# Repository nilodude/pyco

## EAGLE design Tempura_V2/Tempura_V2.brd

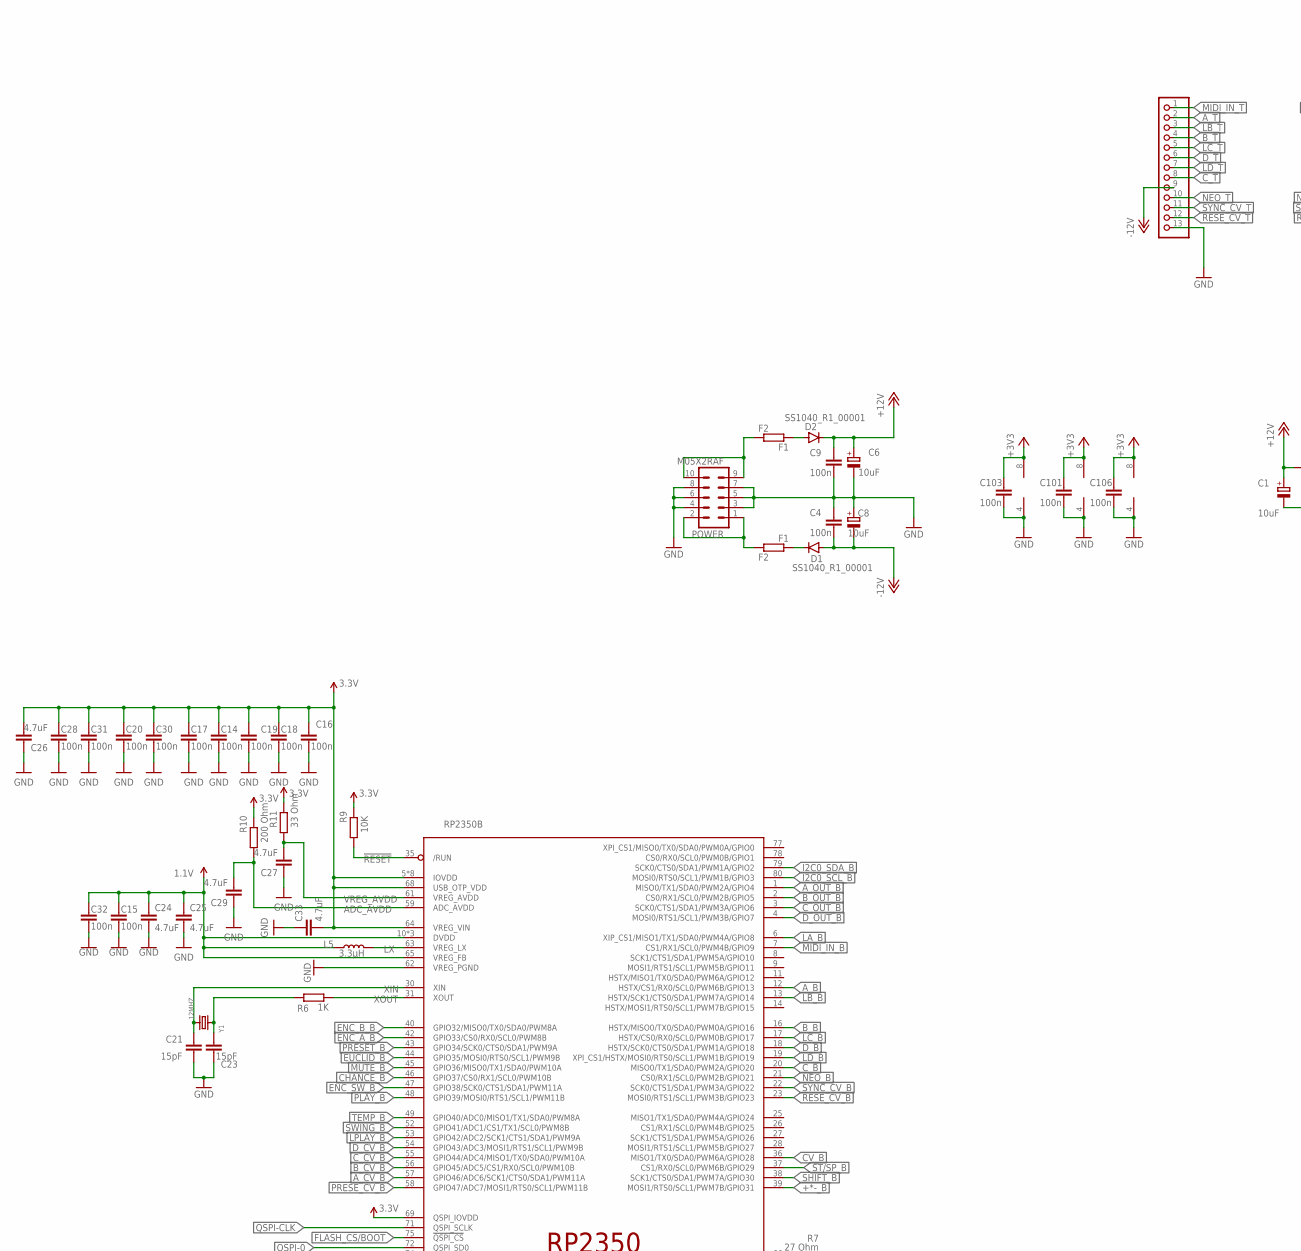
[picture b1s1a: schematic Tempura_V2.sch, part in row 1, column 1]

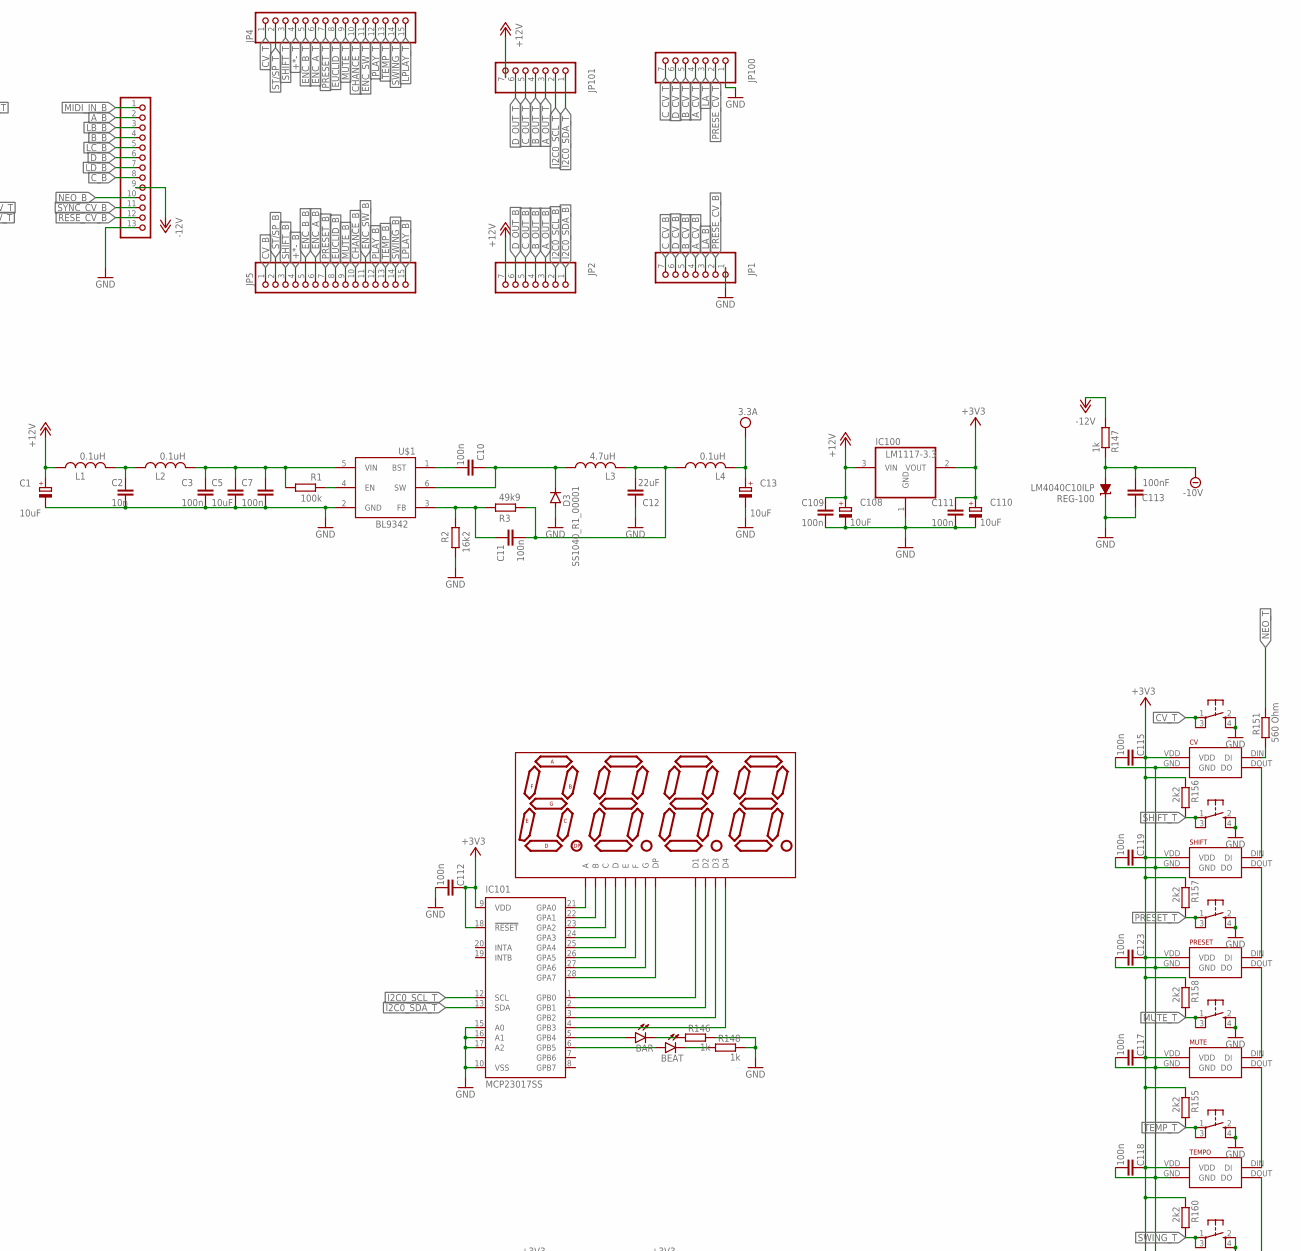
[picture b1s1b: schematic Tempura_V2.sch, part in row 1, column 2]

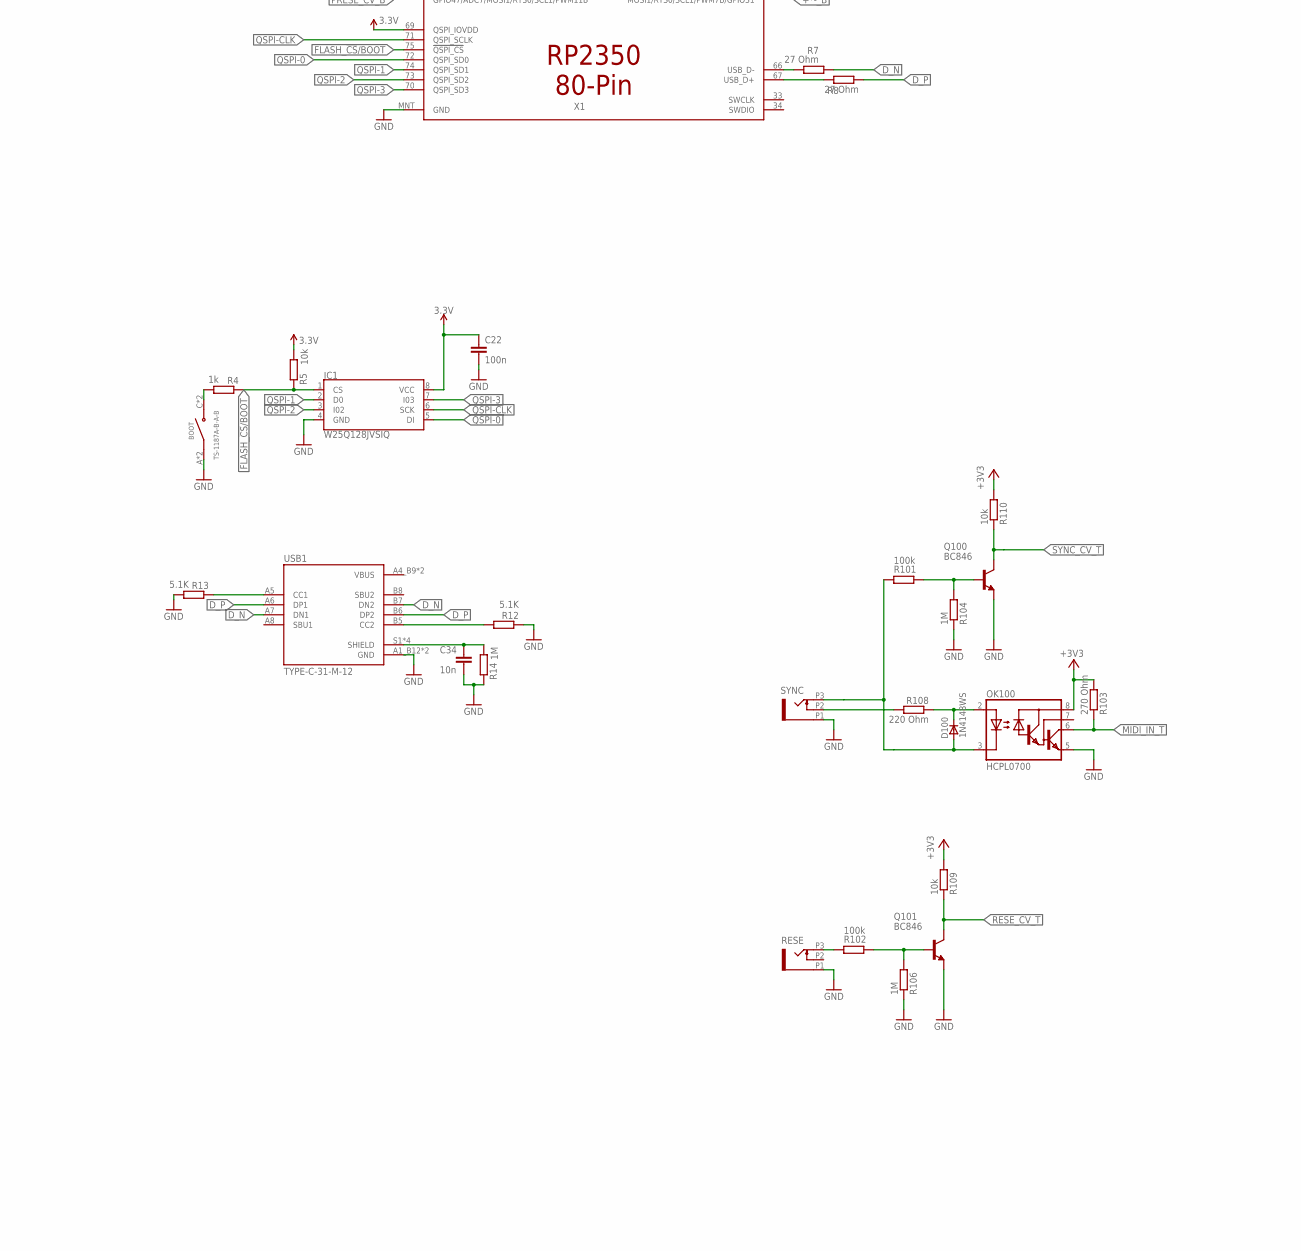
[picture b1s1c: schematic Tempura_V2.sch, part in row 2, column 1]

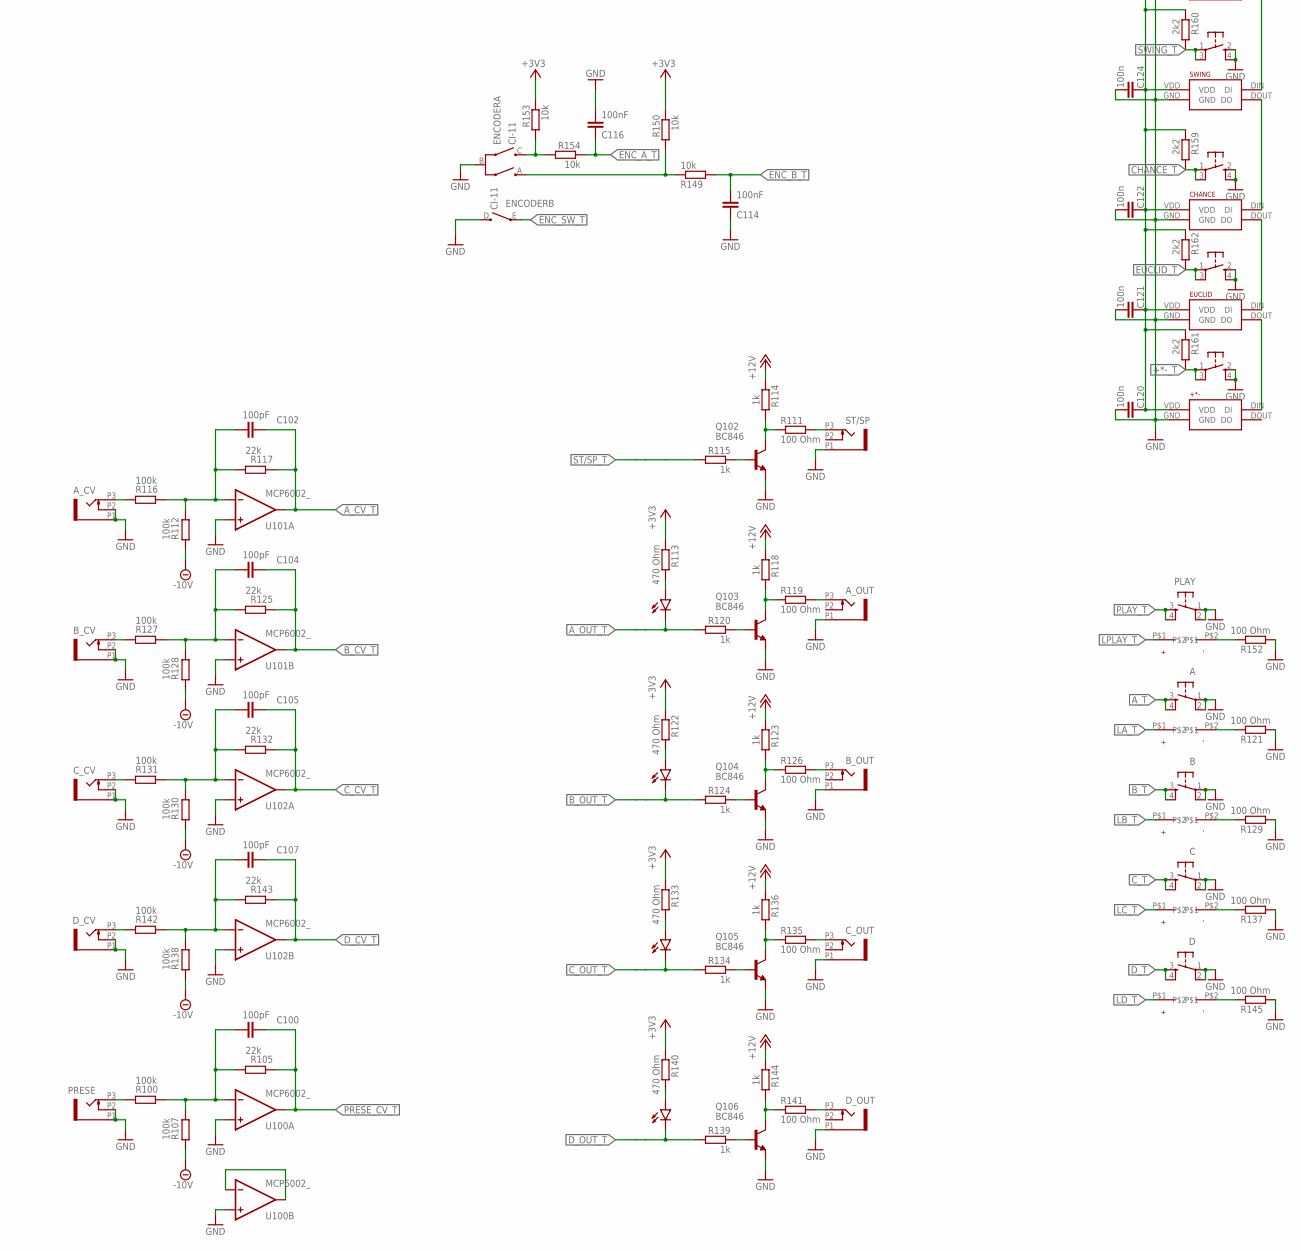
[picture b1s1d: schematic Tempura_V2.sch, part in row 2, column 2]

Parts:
+*-: BUTTON_NEOPIXELBUTTON_PIXEL_ç; BUTTON_PIXEL_ç
A: DTS-6_LED; TIMEBUTTON_HOLES_LEDS
A_CV: OG-PJ301_PJ301_THONKICONNNOHOLER; NOHOLER_GND_SHORT_PADMINI_GND
A_OUT: OG-PJ301_PJ301_THONKICONNNOHOLER; NOHOLER_GND_SHORT_PADMINI_GND
B: DTS-6_LED; TIMEBUTTON_HOLES_LEDS
BAR: OSG5TA7NE4B; LED3MM
BEAT: OSO5JA7NE4B; LED3MM
BOOT: TS-1187A-B-A-B; SW_TS-1187A-B-A-B
B_CV: OG-PJ301_PJ301_THONKICONNNOHOLER; NOHOLER_GND_SHORT_PADMINI_GND
B_OUT: OG-PJ301_PJ301_THONKICONNNOHOLER; NOHOLER_GND_SHORT_PADMINI_GND
C: DTS-6_LED; TIMEBUTTON_HOLES_LEDS
C1, C6, C8, C13, C108, C110: 10uF; PANASONIC_B
C2, C34: 10n; C0603
C3, C4, C7, C9, C10, C11, C22, C101, C103, C106, C109, C111, C112, C115, C117, C118, C119, C120, C121, C122, C123, C124: 100n; C0603
C5: 10uF; C0603
C12: 22uF; C0603
C14, C15, C16, C17, C18, C19, C20, C28, C30, C31, C32: 100n; 0603
C21, C23: 15pF; 0603
C24, C25: 4.7uF; 0603
C26: 4.7uF; C0603
C27, C29, C33: 4.7uF; C0805
C100, C102, C104, C105, C107: 100pF; C0603
C113, C114, C116: 100nF; C0603
CHANCE: BUTTON_NEOPIXELBUTTON_PIXEL_ç; BUTTON_PIXEL_ç
CV: BUTTON_NEOPIXELBUTTON_PIXEL_ç; BUTTON_PIXEL_ç
C_CV: OG-PJ301_PJ301_THONKICONNNOHOLER; NOHOLER_GND_SHORT_PADMINI_GND
C_OUT: OG-PJ301_PJ301_THONKICONNNOHOLER; NOHOLER_GND_SHORT_PADMINI_GND
D: DTS-6_LED; TIMEBUTTON_HOLES_LEDS
D1, D2, D3: SS1040_R1_00001; SOD123
D100: 1N4148WS; SOD323F
D_CV: OG-PJ301_PJ301_THONKICONNNOHOLER; NOHOLER_GND_SHORT_PADMINI_GND
D_OUT: OG-PJ301_PJ301_THONKICONNNOHOLER; NOHOLER_GND_SHORT_PADMINI_GND
ENCODER: CI-11
EUCLID: BUTTON_NEOPIXELBUTTON_PIXEL_ç; BUTTON_PIXEL_ç
F1: F2; R0603
F2: F1; R0603
IC1: W25Q128JVSIQ; SOIC-8
IC100: LM1117-3.3; SOT223
IC101: MCP23017SS; SSOP28
JP1, JP2, JP100, JP101: PINHD-1X7ç; 1X07ç
JP3, JP102: PINHD-1X131X13ç; 1X13ç
JP4, JP5: PINHD-1X151X15ç; 1X15ç
L1, L2, L4: 0.1uH; L3225P
L3: 4.7uH; L3225P
L5: 3.3μH; 1008(2520)
LED_A_OUT: 2 MM LED; LED3MM
LED_B_OUT: 2 MM LED; LED3MM
LED_C_OUT: 2 MM LED; LED3MM
LED_D_OUT: 2 MM LED; LED3MM
LFD36BUE-101B: 7-SEGMENT-4DIGIT-20MM; 7-SEGMENT-4DIGIT-30MM
MUTE: BUTTON_NEOPIXELBUTTON_PIXEL_ç; BUTTON_PIXEL_ç
OK100: HCPL0700; SOIC08
PLAY: DTS-6_LED; TIMEBUTTON_HOLES_LEDS
POWER: M05X2RAF; 2X5-POWER_ACODADO
PRESE: OG-PJ301_PJ301_THONKICONNNOHOLER; NOHOLER_GND_SHORT_PADMINI_GND
PRESET: BUTTON_NEOPIXELBUTTON_PIXEL_ç; BUTTON_PIXEL_ç
Q100, Q101, Q102, Q103, Q104, Q105, Q106: BC846; SOT23
R1, R100, R101, R102, R107, R112, R116, R127, R128, R130, R131, R138, R142: 100k; R0603
R2: 16k2; R0603
R3: 49k9; R0603
R4, R114, R115, R118, R120, R123, R124, R134, R136, R139, R144, R146, R147, R148: 1k; R0603
R5, R109, R110, R149, R150, R153, R154: 10k; R0603
R6: 1K; R0603
R7, R8: 27 Ohm; R0603
R9: 10K; R0603
R10: 200 Ohm; R0603
R11: 33 Ohm; R0603
R12, R13: 5.1K; R0603
R14, R104, R106: 1M; R0603
R103: 270 Ohm; R0603
R105, R117, R125, R132, R143: 22k; R0603
R108: 220 Ohm; R0603
R111, R119, R121, R126, R129, R135, R137, R141, R145, R152: 100 Ohm; R0603
R113, R122, R133, R140: 470 Ohm; R0603
R151: 560 Ohm; R0603
R155, R156, R157, R158, R159, R160, R161, R162: 2k2; R0603
REG-100: LM4040C10ILP; DBZ_R-PDSO-G3
RESE: OG-PJ301_PJ301_THONKICONNNOHOLER; NOHOLER_GND_SHORT_PADMINI_GND
SHIFT: BUTTON_NEOPIXELBUTTON_PIXEL_ç; BUTTON_PIXEL_ç
ST/SP: OG-PJ301_PJ301_THONKICONNNOHOLER; NOHOLER_GND_SHORT_PADMINI_GND
SWING: BUTTON_NEOPIXELBUTTON_PIXEL_ç; BUTTON_PIXEL_ç
SYNC: OG-PJ301_PJ301_THONKICONNNOHOLER; NOHOLER_GND_SHORT_PADMINI_GND
TEMPO: BUTTON_NEOPIXELBUTTON_PIXEL_ç; BUTTON_PIXEL_ç
U100, U101, U102: MCP6002_; SO08
U$1: BL9342; SOT23-6
USB1: TYPE-C-31-M-12; HRO_TYPE-C-31-M-12
X1: RP2350B; QFN80
Y1: 12MHZ; CRYSTAL_3.2X2.5

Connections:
1.1V: C15.1, C24.1, C25.1, C32.1, L5.1, X1.10 (DVDD), X1.32 (DVDD), X1.51 (DVDD), X1.65 (VREG_FB)
!RESET: R9.1, X1.35 (/RUN)
+3V3: +*-.VDD, C101.1, C103.1, C106.1, C110.+, C111.1, C112.1, C115.1, C117.1, C118.1, C119.1, C120.1, C121.1, C122.1, C123.1, C124.1, CHANCE.VDD, CV.VDD, EUCLID.VDD, IC100.2 (VOUT), IC101.9 (VDD), IC101.18 (!RESET), MUTE.VDD, OK100.8 (VCC), PRESET.VDD, R103.2, R109.2, R110.2, R113.1, R122.1, R133.1, R140.1, R150.1, R153.1, R155.2, R156.2, R157.2, R158.2, R159.2, R160.2, R161.2, R162.2, SHIFT.VDD, SWING.VDD, TEMPO.VDD, U100.8 (V+), U101.8 (V+), U102.8 (V+)
+12V: C1.+, C6.+, C9.1, C108.+, C109.1, D2.C, IC100.3 (VIN), JP2.7, JP101.7, L1.1, R114.1, R118.1, R123.1, R136.1, R144.1
+*-_B: JP5.4, X1.39 (MOSI1/RTS0/SCL1/PWM7B/GPIO31)
+*-_T: +*-.1, +*-.3, JP4.4, R161.1
-10V: C113.2, R107.2, R112.2, R128.2, R130.2, R138.2, R147.1, REG-100.2 (A)
-12V: C4.2, C8.-, D1.A, JP3.9, JP102.9, R147.2
ADC_AVDD: C29.2, R10.1, X1.59 (ADC_AVDD)
A_B: JP3.2, X1.12 (HSTX/CS1/RX0/SCL0/PWM6B/GPIO13)
A_CV_B: JP1.4, X1.57 (GPIO46/ADC6/SCK1/CTS0/SDA1/PWM11A)
A_CV_T: C102.2, JP100.4, R117.1, U101.1 (OUT)
A_OUT_B: JP2.3, X1.1 (MISO0/TX1/SDA0/PWM2A/GPIO4)
A_OUT_T: JP101.3, LED_A_OUT.K (C), R120.2
A_T: A.3, A.4, JP102.2
B_B: JP3.4, X1.16 (HSTX/MISO0/TX0/SDA0/PWM0A/GPIO16)
B_CV_B: JP1.5, X1.56 (GPIO45/ADC5/CS1/RX0/SCL0/PWM10B)
B_CV_T: C104.2, JP100.5, R125.1, U101.7 (OUT)
B_OUT_B: JP2.4, X1.2 (CS0/RX1/SCL0/PWM2B/GPIO5)
B_OUT_T: JP101.4, LED_B_OUT.K (C), R124.2
B_T: B.3, B.4, JP102.4
CHANCE_B: JP5.10, X1.46 (GPIO37/CS0/RX1/SCL0/PWM10B)
CHANCE_T: CHANCE.1, CHANCE.3, JP4.10, R159.1
CV_B: JP5.1, X1.36 (MISO1/TX0/SDA0/PWM6A/GPIO28)
CV_T: CV.1, CV.3, JP4.1
C_B: JP3.8, X1.20 (MISO0/TX1/SDA0/PWM2A/GPIO20)
C_CV_B: JP1.7, X1.55 (GPIO44/ADC4/MISO1/TX0/SDA0/PWM10A)
C_CV_T: C105.2, JP100.7, R132.1, U102.1 (OUT)
C_OUT_B: JP2.5, X1.3 (SCK0/CTS1/SDA1/PWM3A/GPIO6)
C_OUT_T: JP101.5, LED_C_OUT.K (C), R134.2
C_T: C.3, C.4, JP102.8
DO_N: R7.2, X1.66 (USB_D-)
DO_P: R8.2, X1.67 (USB_D+)
D_B: JP3.6, X1.18 (HSTX/SCK0/CTS0/SDA1/PWM1A/GPIO18)
D_CV_B: JP1.6, X1.54 (GPIO43/ADC3/MOSI1/RTS1/SCL1/PWM9B)
D_CV_T: C107.2, JP100.6, R143.1, U102.7 (OUT)
D_N: R7.1, USB1.A7 (DN1), USB1.B7 (DN2)
D_OUT_B: JP2.6, X1.4 (MOSI0/RTS1/SCL1/PWM3B/GPIO7)
D_OUT_T: JP101.6, LED_D_OUT.K (C), R139.2
D_P: R8.1, USB1.A6 (DP1), USB1.B6 (DP2)
D_T: D.3, D.4, JP102.6
ENC_A_B: JP5.6, X1.42 (GPIO33/CS0/RX0/SCL0/PWM8B)
ENC_A_T: C116.1, JP4.6, R154.1
ENC_B_B: JP5.5, X1.40 (GPIO32/MISO0/TX0/SDA0/PWM8A)
ENC_B_T: C114.2, JP4.5, R149.2
ENC_SW_B: JP5.11, X1.47 (GPIO38/SCK0/CTS1/SDA1/PWM11A)
ENC_SW_T: ENCODER.E, JP4.11
EUCLID_B: JP5.8, X1.44 (GPIO35/MOSI0/RTS0/SCL1/PWM9B)
EUCLID_T: EUCLID.1, EUCLID.3, JP4.8, R162.1
FLASH_!CS!/BOOT: IC1.1 (CS), R4.1, R5.1, X1.75 (!QSPI_CS)
GND: +*-.2, +*-.4, +*-.GND, A.1, A.2, A_CV.P1 (1), A_CV.P2 (2), A_OUT.P1 (1), B.1, B.2, BOOT.A (COM), BOOT.B (COM), B_CV.P1 (1), B_CV.P2 (2), B_OUT.P1 (1), C.1, C.2, C1.-, C2.2, C3.2, C4.1, C5.2, C6.-, C7.2, C8.+, C9.2, C12.1, C13.-, C14.2, C15.2, C16.2, C17.2, C18.2, C19.2, C20.2, C21.2, C22.2, C23.2, C24.2, C25.2, C26.1, C27.1, C28.2, C29.1, C30.2, C31.2, C32.2, C33.1, C34.2, C101.2, C103.2, C106.2, C108.-, C109.2, C110.-, C111.2, C112.2, C113.1, C114.1, C115.2, C116.2, C117.2, C118.2, C119.2, C120.2, C121.2, C122.2, C123.2, C124.2, CHANCE.2, CHANCE.4, CHANCE.GND, CV.2, CV.4, CV.GND, C_CV.P1 (1), C_CV.P2 (2), C_OUT.P1 (1), D.1, D.2, D3.A, D_CV.P1 (1), D_CV.P2 (2), D_OUT.P1 (1), ENCODER.B (C), ENCODER.D, EUCLID.2, EUCLID.4, EUCLID.GND, IC1.4 (GND), IC100.1 (GND), IC101.10 (VSS), IC101.15 (A0), IC101.16 (A1), IC101.17 (A2), JP1.1, JP3.13, JP100.1, JP102.13, MUTE.2, MUTE.4, MUTE.GND, OK100.5 (GND), PLAY.1, PLAY.2, POWER.3, POWER.4, POWER.5, POWER.6, POWER.7, POWER.8, PRESE.P1 (1), PRESE.P2 (2), PRESET.2, PRESET.4, PRESET.GND, Q100.2 (E), Q101.2 (E), Q102.2 (E), Q103.2 (E), Q104.2 (E), Q105.2 (E), Q106.2 (E), R2.1, R12.1, R13.2, R14.1, R104.1, R106.1, R121.2, R129.2, R137.2, R145.2, R146.1, R148.1, R152.2, REG-100.1 (C), RESE.P1 (1), SHIFT.2, SHIFT.4, SHIFT.GND, ST/SP.P1 (1), SWING.2, SWING.4, SWING.GND, SYNC.P1 (1), TEMPO.2, TEMPO.4, TEMPO.GND, U100.3 (+IN), U100.4 (V-), U100.5 (+IN), U101.3 (+IN), U101.4 (V-), U101.5 (+IN), U102.3 (+IN), U102.4 (V-), U102.5 (+IN), U$1.2 (GND), USB1.A1_B12 (GND), USB1.B1_A12 (GND), X1.62 (VREG_PGND), X1.MNT (GND)
I2C0_SCL_B: JP2.2, X1.80 (MOSI0/RTS0/SCL1/PWM1B/GPIO3)
I2C0_SCL_T: IC101.12 (SCL), JP101.2
I2C0_SDA_B: JP2.1, X1.79 (SCK0/CTS0/SDA1/PWM1A/GPIO2)
I2C0_SDA_T: IC101.13 (SDA), JP101.1
LA_B: JP1.3, X1.6 (XIP_CS1/MISO1/TX1/SDA0/PWM4A/GPIO8)
LA_T: A.P$1, JP100.3
LB_B: JP3.3, X1.13 (HSTX/SCK1/CTS0/SDA1/PWM7A/GPIO14)
LB_T: B.P$1, JP102.3
LC_B: JP3.5, X1.17 (HSTX/CS0/RX0/SCL0/PWM0B/GPIO17)
LC_T: C.P$1, JP102.5
LD_B: JP3.7, X1.19 (XPI_CS1/HSTX/MOSI0/RTS0/SCL1/PWM1B/GPIO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)
LD_T: D.P$1, JP102.7
LPLAY_B: JP5.15, X1.53 (GPIO42/ADC2/SCK1/CTS1/SDA1/PWM9A)
LPLAY_T: JP4.15, PLAY.P$1
LX: L5.2, X1.63 (VREG_LX)
MIDI_IN_B: JP3.1, X1.7 (CS1/RX1/SCL0/PWM4B/GPIO9)
MIDI_IN_T: JP102.1, OK100.6 (VO), R103.1
MUTE_B: JP5.9, X1.45 (GPIO36/MISO0/TX1/SDA0/PWM10A)
MUTE_T: JP4.9, MUTE.1, MUTE.3, R158.1
unnamed: R1.2, U$1.4 (EN)
unnamed: C3.1, C5.1, C7.1, L2.2, R1.1, U$1.5 (VIN)
unnamed: C2.1, L1.2, L2.1
unnamed: C10.2, U$1.1 (BST)
unnamed: C10.1, D3.C, L3.1, U$1.6 (SW)
unnamed: C11.1, R2.2, R3.2, U$1.3 (FB)
unnamed: C11.2, C12.2, L3.2, L4.1, R3.1
unnamed: IC101.21 (GPA0), LFD36BUE-101B.11 (A)
unnamed: BAR.A, IC101.5 (GPB4)
unnamed: D100.C, OK100.2 (A), R108.1
unnamed: IC101.22 (GPA1), LFD36BUE-101B.7 (B)
unnamed: IC101.23 (GPA2), LFD36BUE-101B.4 (C)
unnamed: IC101.24 (GPA3), LFD36BUE-101B.2 (D)
unnamed: IC101.25 (GPA4), LFD36BUE-101B.1 (E)
unnamed: IC101.26 (GPA5), LFD36BUE-101B.10 (F)
unnamed: IC101.27 (GPA6), LFD36BUE-101B.5 (G)
unnamed: IC101.28 (GPA7), LFD36BUE-101B.3 (DP)
unnamed: IC101.1 (GPB0), LFD36BUE-101B.12 (D1)
unnamed: IC101.2 (GPB1), LFD36BUE-101B.9 (D2)
unnamed: IC101.3 (GPB2), LFD36BUE-101B.8 (D3)
unnamed: IC101.4 (GPB3), LFD36BUE-101B.6 (D4)
unnamed: C102.1, R112.1, R116.1, R117.2, U101.2 (-IN)
unnamed: CV.DIN (DI), R151.2
unnamed: CV.DOUT (DO), SHIFT.DIN (DI)
unnamed: PRESET.DIN (DI), SHIFT.DOUT (DO)
unnamed: MUTE.DIN (DI), PRESET.DOUT (DO)
unnamed: MUTE.DOUT (DO), TEMPO.DIN (DI)
unnamed: CHANCE.DOUT (DO), EUCLID.DIN (DI)
unnamed: +*-.DIN (DI), EUCLID.DOUT (DO)
unnamed: U100.6 (-IN), U100.7 (OUT)
unnamed: C104.1, R125.2, R127.1, R128.1, U101.6 (-IN)
unnamed: C105.1, R130.1, R131.1, R132.2, U102.2 (-IN)
unnamed: C107.1, R138.1, R142.1, R143.2, U102.6 (-IN)
unnamed: PLAY.P$2, R152.1
unnamed: A.P$2, R121.1
unnamed: B.P$2, R129.1
unnamed: F2.2, POWER.9, POWER.10
unnamed: D2.A, F2.1
unnamed: F1.2, POWER.1, POWER.2
unnamed: D1.C, F1.1
unnamed: C.P$2, R137.1
unnamed: D.P$2, R145.1
unnamed: A_OUT.P3 (3), R119.2
unnamed: B_OUT.P3 (3), R126.2
unnamed: Q100.1 (B), R101.1, R104.2
unnamed: C_OUT.P3 (3), R135.2
unnamed: Q101.1 (B), R102.1, R106.2
unnamed: D_OUT.P3 (3), R141.2
unnamed: Q102.1 (B), R115.1
unnamed: A_CV.P3 (3), R116.2
unnamed: B_CV.P3 (3), R127.2
unnamed: C_CV.P3 (3), R131.2
unnamed: D_CV.P3 (3), R142.2
unnamed: R111.2, ST/SP.P3 (3)
unnamed: Q102.3 (C), R111.1, R114.2
unnamed: D100.A, OK100.3 (C), R101.2, SYNC.P3 (3)
unnamed: PRESE.P3 (3), R100.2
unnamed: R102.2, RESE.P3 (3)
unnamed: ENCODER.A, R149.1, R150.2
unnamed: ENCODER.C (B), R153.2, R154.2
unnamed: BAR.K (C), R146.2
unnamed: BEAT.A, IC101.6 (GPB5)
unnamed: BEAT.K (C), R148.2
unnamed: CHANCE.DIN (DI), SWING.DOUT (DO)
unnamed: C100.1, R100.1, R105.2, R107.1, U100.2 (-IN)
unnamed: Q103.1 (B), R120.1
unnamed: Q103.3 (C), R118.2, R119.1
unnamed: LED_A_OUT.A, R113.2
unnamed: R108.2, SYNC.P2 (2)
unnamed: Q104.1 (B), R124.1
unnamed: Q104.3 (C), R123.2, R126.1
unnamed: LED_B_OUT.A, R122.2
unnamed: Q105.1 (B), R134.1
unnamed: Q105.3 (C), R135.1, R136.2
unnamed: LED_C_OUT.A, R133.2
unnamed: Q106.1 (B), R139.1
unnamed: Q106.3 (C), R141.1, R144.2
unnamed: LED_D_OUT.A, R140.2
unnamed: SWING.DIN (DI), TEMPO.DOUT (DO)
unnamed: C23.1, R6.2, Y1.2
unnamed: BOOT.C (NO), BOOT.D (NO), R4.2
unnamed: C34.1, R14.2, USB1.S1 (SHIELD), USB1.S2 (SHIELD), USB1.S3 (SHIELD), USB1.S4 (SHIELD)
unnamed: R13.1, USB1.A5 (CC1)
unnamed: R12.2, USB1.B5 (CC2)
NEO_B: JP3.10, X1.21 (CS0/RX1/SCL0/PWM2B/GPIO21)
NEO_T: JP102.10, R151.1
PLAY_B: JP5.12, X1.48 (GPIO39/MOSI0/RTS1/SCL1/PWM11B)
PLAY_T: JP4.12, PLAY.3, PLAY.4
PRESET_B: JP5.7, X1.43 (GPIO34/SCK0/CTS0/SDA1/PWM9A)
PRESET_T: JP4.7, PRESET.1, PRESET.3, R157.1
PRESE_CV_B: JP1.2, X1.58 (GPIO47/ADC7/MOSI1/RTS0/SCL1/PWM11B)
PRESE_CV_T: C100.2, JP100.2, R105.1, U100.1 (OUT)
QSPI-0: IC1.5 (DI), X1.72 (QSPI_SD0)
QSPI-1: IC1.2 (D0), X1.74 (QSPI_SD1)
QSPI-2: IC1.3 (I02), X1.73 (QSPI_SD2)
QSPI-3: IC1.7 (I03), X1.70 (QSPI_SD3)
QSPI-CLK: IC1.6 (SCK), X1.71 (QSPI_SCLK)
RESE_CV_B: JP3.12, X1.23 (MOSI0/RTS1/SCL1/PWM3B/GPIO23)
RESE_CV_T: JP102.12, Q101.3 (C), R109.1
SHIFT_B: JP5.3, X1.38 (SCK1/CTS0/SDA1/PWM7A/GPIO30)
SHIFT_T: JP4.3, R156.1, SHIFT.1, SHIFT.3
ST/SP_B: JP5.2, X1.37 (CS1/RX0/SCL0/PWM6B/GPIO29)
ST/SP_T: JP4.2, R115.2
SWING_B: JP5.14, X1.52 (GPIO41/ADC1/CS1/TX1/SCL0/PWM8B)
SWING_T: JP4.14, R160.1, SWING.1, SWING.3
SYNC_CV_B: JP3.11, X1.22 (SCK0/CTS1/SDA1/PWM3A/GPIO22)
SYNC_CV_T: JP102.11, Q100.3 (C), R110.1
TEMP_B: JP5.13, X1.49 (GPIO40/ADC0/MISO1/TX1/SDA0/PWM8A)
TEMP_T: JP4.13, R155.1, TEMPO.1, TEMPO.3
VBUS: USB1.A4_B9 (VBUS), USB1.B4_A9 (VBUS)
VCC: C13.+, C14.1, C16.1, C17.1, C18.1, C19.1, C20.1, C22.1, C26.2, C28.1, C30.1, C31.1, C33.2, IC1.8 (VCC), L4.2, R5.2, R9.2, R10.2, R11.2, X1.5 (IOVDD), X1.15 (IOVDD), X1.24 (IOVDD), X1.29 (IOVDD), X1.41 (IOVDD), X1.50 (IOVDD), X1.60 (IOVDD), X1.64 (VREG_VIN), X1.68 (USB_OTP_VDD), X1.69 (QSPI_IOVDD), X1.76 (IOVDD)
VREG_AVDD: C27.2, R11.1, X1.61 (VREG_AVDD)
XIN: C21.1, X1.30 (XIN), Y1.1
XOUT: R6.1, X1.31 (XOUT)

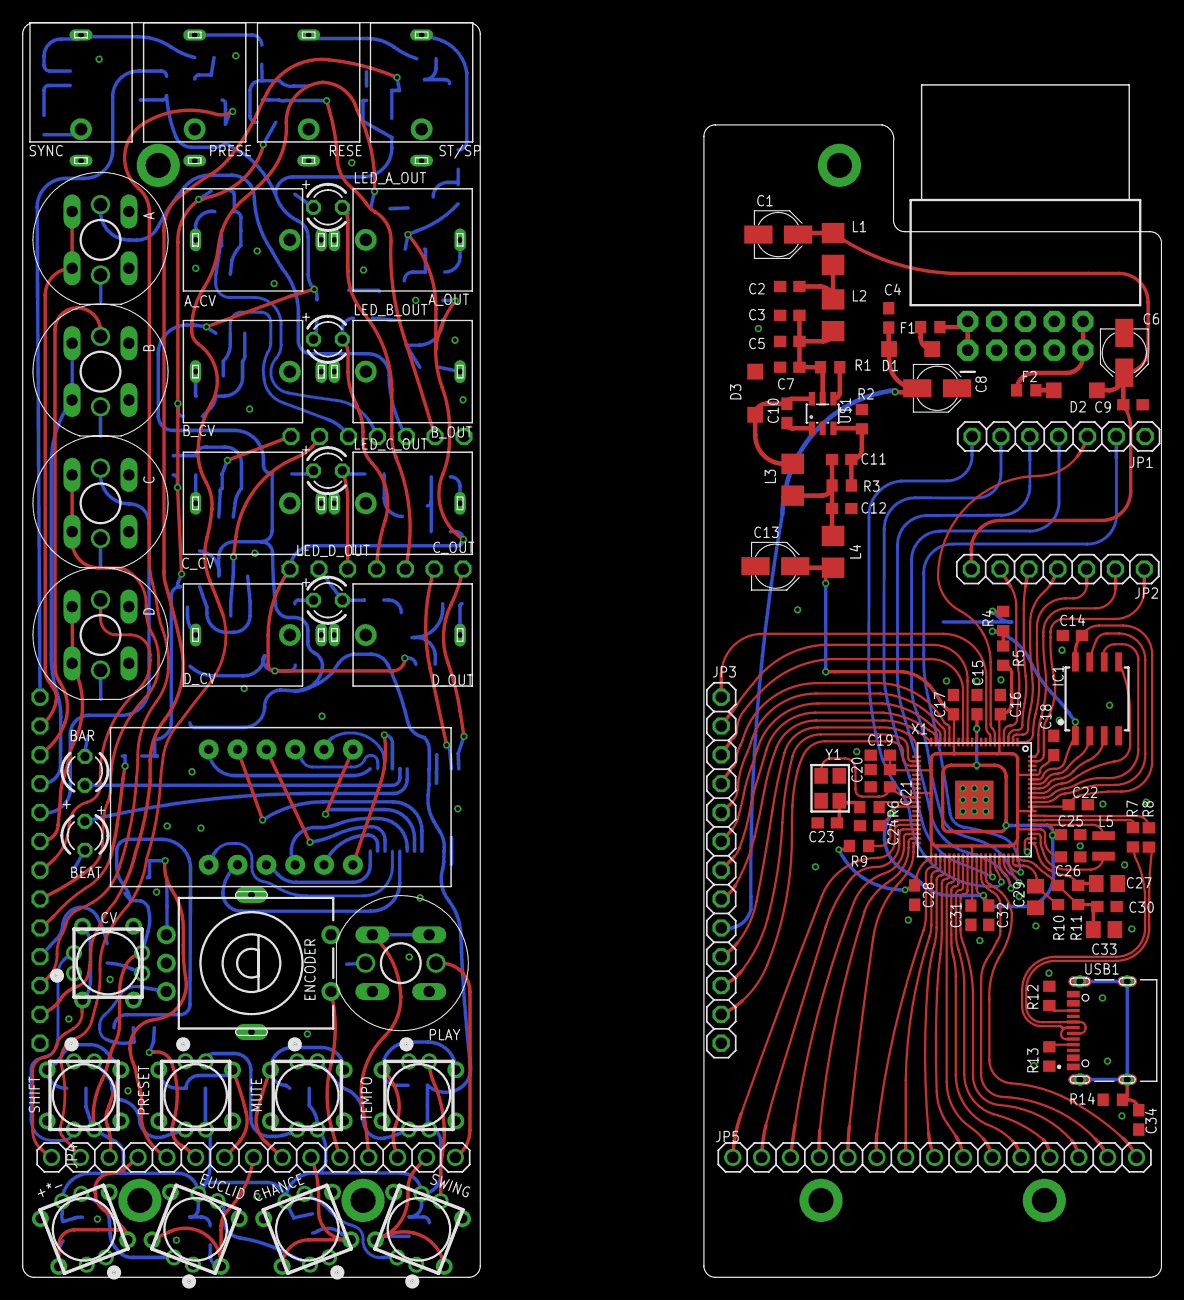
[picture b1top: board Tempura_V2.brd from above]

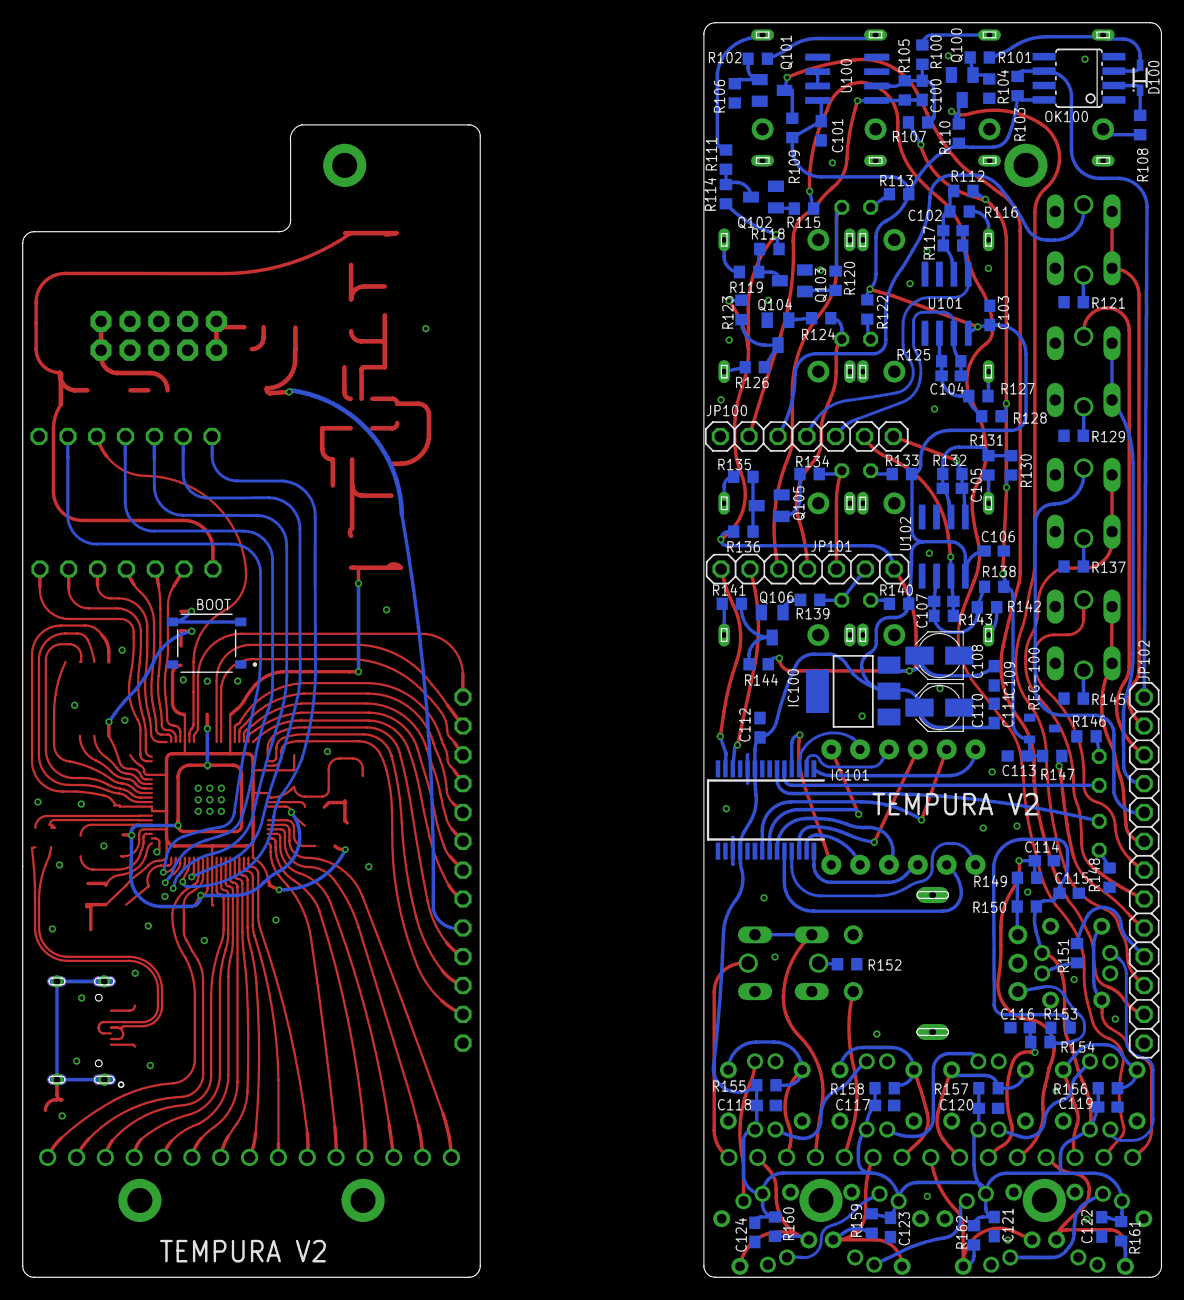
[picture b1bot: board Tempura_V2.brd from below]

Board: 2 copper layers, 100.3 x 110.5 mm, 210 parts (107 on the bottom side), 184 nets.

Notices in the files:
parts and their libraries:
SparkFun: Licensing: CC v3.0 Share-Alike You are welcome to use this library for commercial purposes.
SparkFun-IC-Memory: Licensing: Creative Commons ShareAlike 4.0 International - https://creativecommons.org/licenses/by-sa/4.0
